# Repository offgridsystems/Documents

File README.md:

# DKblock documents -  
Here is the DK website for more information: https://dkblock922508958.wordpress.com 

Here is the ebay store for some parts. Let me know at the "Contact" tab of Wordpress (or ebay) if there is something else you would like.
https://www.ebay.com/sch/i.html?_from=R40&_trksid=p2380057.m570.l1313.TR0.TRC0.A0.H0.Xdkblock.TRS4&_nkw=dkblock&_sacat=0

All documents can be opened in OpenOffice format or Adobe Acrobat Reader. Some drawing files are in Alibre Design (for example AD_DRW extension). Please note that if your CAD program cannot read these files, not to worry because most CAD programs can output formats that can be read by other CAD programs, so please ask if you would like another format, we will try to accomodate.

All DKblock software and hardware is released as open source hardware (OSHW) as defined by the OSHWA: https://www.oshwa.org/definition/ and under the JSON license defined at https://www.json.org/license.html

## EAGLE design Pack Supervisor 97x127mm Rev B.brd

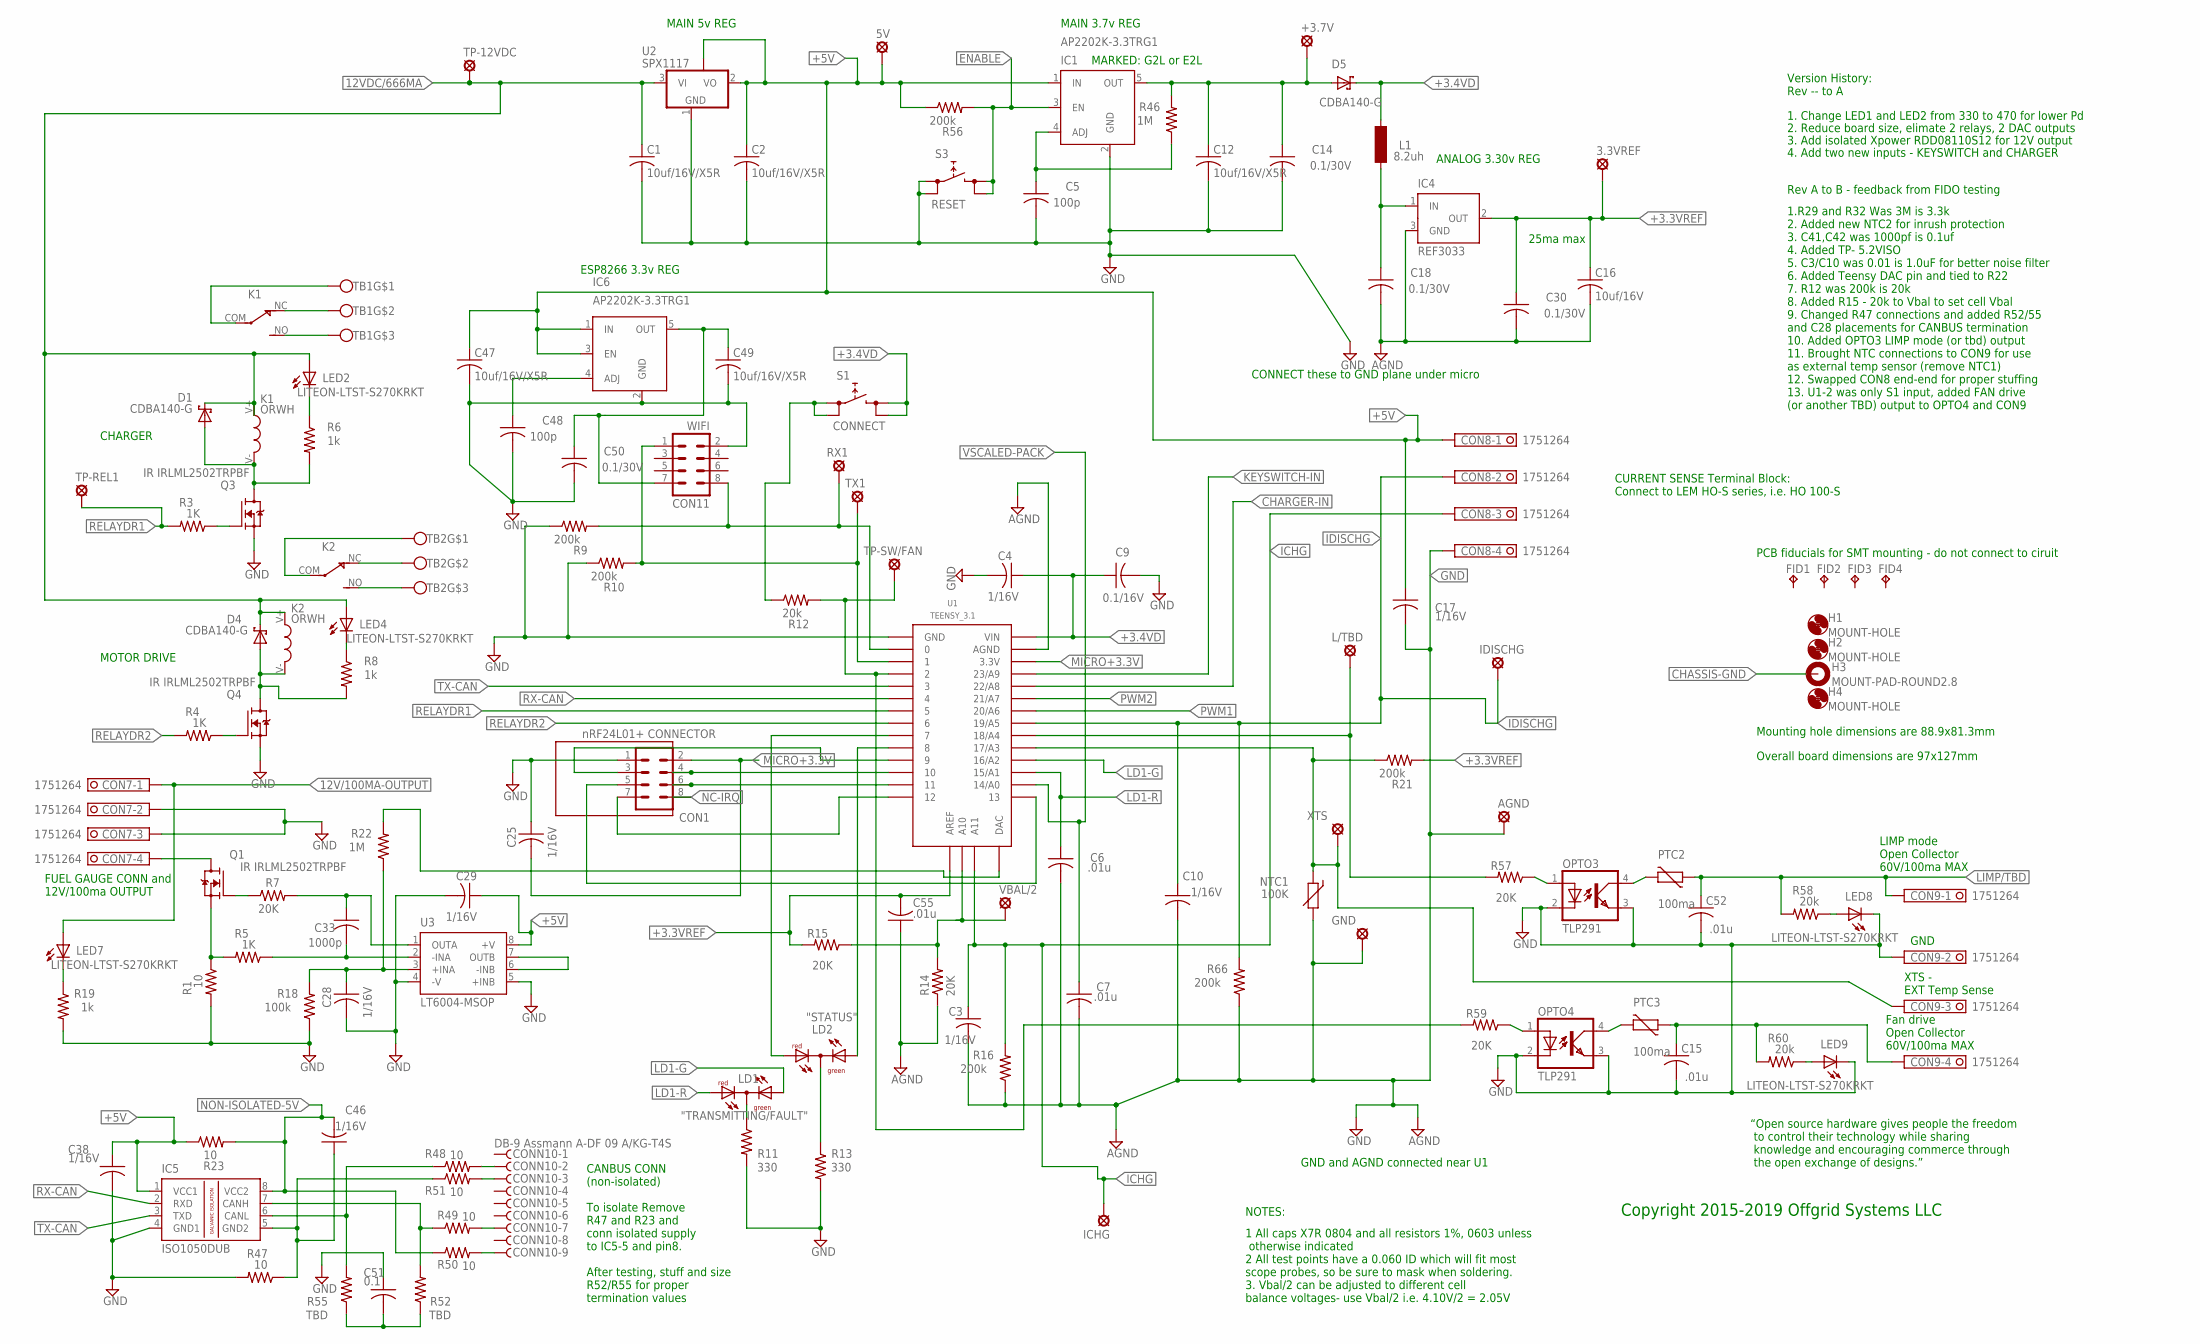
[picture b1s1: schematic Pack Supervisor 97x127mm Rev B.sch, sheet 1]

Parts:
3.3VREF, 5V: LSP10
+3.7V: LSP10
AGND: LSP10
C1, C2, C12, C47, C49: 10uf/16V/X5R; C0805K; MPN Murata GRM21BR61C106ME15L
C3, C10: 1/16V; TIMS_INDUCTOR_C0805; MPN Kemet C0805C103K5RACTU
C4, C17, C25, C28, C29, C38, C46: 1/16V; TIMS_INDUCTOR_C0805; MPN Kemet C0805C105K4RACTU
C5, C48: 100p; TIMS_INDUCTOR_C0805; MPN Kemet C0805C104K5RACTU
C6, C7, C15, C52: .01u; TIMS_INDUCTOR_C0805; MPN Kemet C0805C103K5RACTU
C9: 0.1/16V; TIMS_INDUCTOR_C0805; MPN Kemet C0805C104K5RACTU
C14, C18, C30, C50: 0.1/30V; TIMS_INDUCTOR_C0805; MPN Kemet C0805C104K5RACTU
C16: 10uf/16V; C0805K; MPN Murata GRM21BR61A476ME15L
C33: 1000p; TIMS_INDUCTOR_C0805; MPN Kemet C0805C105K4RACTU
C51: 0.1; TIMS_INDUCTOR_C0805; MPN Kemet C0805C105K4RACTU
C55: .01u; C0805; MPN Welwyn PCF0603R-3K01BT1
CON1: nRF24L01+ CONNECTOR; NRF24L01
CON7, CON8, CON9: 1751264
CON11: WIFI; MA04-2; MPN Sullins PPPC042LFBN-RC
CONN10: DB-9 Assmann A-DF 09 A/KG-T4S; H5M09RA; MPN ASSMANN A-DS 09 A/KG-T4S
D1, D4, D5: CDBA140-G; DO214AC; MPN comchip CDBA140-G
FID1, FID2, FID3, FID4: FIDUCIALTP10R; TP10R
GND: LSP10
H1: MOUNT-HOLE; 2,6; MPN Keystone 9056
H2, H4: MOUNT-HOLE; 2,6
H3: MOUNT-PAD-ROUND2.8; 2,8-PAD
IC1, IC6: AP2202K-3.3TRG1; SOT23-5; MPN Diodes AP2202K-3.3TRG1
IC4: REF3033; SOT23; MPN TI REF3033AIDBZR
IC5: ISO1050DUB; DUB-R-PDSO-G8; MPN TI ISO1050DUBR
ICHG: LSP10
IDISCHG: LSP10
K1, K2: ORWH; MPN TE 1461069-5
L1: 8.2uh; SM-1206; MPN Abracon AIML-1206-8R2K-T
L/TBD: LSP10
LD1: "TRANSMITTING/FAULT"; DUOLED-C-5MM; MPN Kingbright WP59EGC
LD2: "STATUS"; DUOLED-C-5MM; MPN Kingbright WP59EGC
LED2, LED4, LED7, LED8, LED9: LITEON-LTST-S270KRKT; MPN LiteOn LTST-S270KSKT
NTC1: 100K; 0603; MPN MURATA NCP18WF104J03RB
OPTO3, OPTO4: TLP291; MINI-FLAT-4
PTC2, PTC3: 100ma; CT/CN0603; MPN Bel Fuse 0ZCM0010FF2G
Q1, Q3, Q4: IRLML2502TRPBF; SOT23; MPN IR IRLML2502TRPBF
R1, R23, R47, R48, R49, R50, R51: 10; R0603; MPN Bourns CR0603-FX-10R0ELF
R3, R4, R5: 1K; R0603; MPN Bourns CR0603-FX-1001ELF
R6, R8, R19: 1k; R0603; MPN Bourns CR0603-FX-3300ELF
R7, R14, R15, R57, R59: 20K; R0603; MPN Bourns CR0603-FX-2002ELF
R9, R10, R16, R21, R56, R66: 200k; R0603; MPN Bourns CR0603-FX-2003ELF
R11, R13: 330; R0603; MPN Bourns CR0603-FX-3300ELF
R12: 20k; R0603; MPN Bourns CR0603-FX-2003ELF
R18: 100k; R0603; MPN Bourns CR0603-FX-1003ELF
R22, R46: 1M; R0603; MPN Bourns CR0603-FX-1004ELF
R52, R55: TBD; 0207/5V
R58, R60: 20k; R0603; MPN Bourns CR0603-FX-1001ELF
RX1: LSP10
S1: CONNECT; PTS645; MPN C&k PTS645SM43SMTR92 LFS
S3: RESET; PTS645; MPN C&k PTS645SM43SMTR92 LFS
TB1, TB2: TE-5-1437652-4; MPN TE 5-1437652-4
TP-12VDC: LSP10
TP-REL1: LSP10
TP-SW/FAN: LSP10
TX1: LSP10
U1: TEENSY_3.1; TEENSY_3.0-DIP+ANALOG+DAC; MPN OshPark Teensy 3.1
U2: SPX1117; SOT223; MPN Exar SPX1117M3-L-5-0/TR
U3: LT6004-MSOP; MPN LTC LT6004CMS8
VBAL/2: LSP10
XTS: LSP10

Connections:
0-UNUSED: CON11.8, R9.2, RX1.MP, U1.0
5V-ESP: C49.1, C50.1, CON11.7, IC6.5 (OUT)
12V/100MA-OUTPUT: CON7.1, LED7.ANODE (A); also elsewhere on the board
12VDC/666MA: C1.1, D1.C, D4.C, K1.V+, K2.V+, LED2.ANODE (A), LED4.ANODE (A), TP-12VDC.MP, U2.3 (VI); also elsewhere on the board
+3.3VREF: 3.3VREF.MP, C16.1, C30.1, C55.2, IC4.2 (OUT), R15.2, R21.2, U1.AREF; also elsewhere on the board
+3.4VD: C4.1, C9.1, D5.C, L1.2, S1.3, S1.4, U1.VIN; also elsewhere on the board
+3.65VD: +3.7V.MP, C12.1, C14.1, D5.A, IC1.5 (OUT), R46.2
+3.300VA: C18.1, IC4.1 (IN), L1.1
+5: CONN10.9, R50.2
+5V: 5V.MP, C2.1, C17.1, C29.1, C38.1, C47.1, CON8.1, IC1.1 (IN), IC5.1 (VCC1), IC6.1 (IN), IC6.3 (EN), R23.1, R56.1, U2.2 (VO), U2.4 (TAB), U3.8 (+V)
ADC-L3: L/TBD.MP, R57.2, U1.18/A4
ADS: D4.A, K2.V-, Q4.3 (D), R8.2
CE: CON1.3, U1.9
CHARGER-IN: U1.22/A8; also elsewhere on the board
CHASSIS-GND: H3.B2,8; also elsewhere on the board
CHI: CONN10.7, R49.2
CLO: CONN10.2, R48.2
CSN: CON1.4, U1.10
DAC: R22.2, U1.14 (DAC)
ENABLE: IC1.3 (EN), R56.2, S3.3, S3.4
FAN/TBD: C15.1, CON9.4, PTC3.1, R60.2
FUELGAUGE: CON7.4, Q1.3 (D)
G: CONN10.3, R51.2
GND: AGND.MP, C1.2, C2.2, C3.2, C4.2, C5.2, C6.2, C7.2, C9.2, C10.2, C12.2, C14.2, C15.2, C16.2, C17.2, C18.2, C25.1, C28.2, C29.2, C30.2, C38.2, C47.2, C48.2, C49.2, C50.2, C51.1, C52.2, C55.1, CON1.1, CON7.2, CON7.3, CON8.4, CON9.2, CON11.2, GND.MP, IC1.2 (GND), IC4.3 (GND), IC5.4 (GND1), IC6.2 (GND), LED8.CATHODE (C), LED9.CATHODE (C), NTC1.2, OPTO3.2 (C), OPTO3.3 (EMIT), OPTO4.2 (C), OPTO4.3 (EMIT), Q3.2 (S), Q4.2 (S), R1.2, R9.1, R10.1, R11.2, R13.2, R14.1, R16.1, R18.1, R19.2, R47.2, R66.1, S3.1, S3.2, U1.AGND, U1.GND, U2.1 (GND), U3.4 (-V), U3.5 (+INB); also elsewhere on the board
ICHG: C3.1, CON8.3, ICHG.MP, R16.2, U1.A11
IDISCHG: C10.1, CON8.2, IDISCHG.MP, R66.2, U1.19/A5
KEYSWITCH-IN: U1.23/A9; also elsewhere on the board
LD1-G: LD1.AX (AG), U1.16/A2
LD1-R: C6.1, LD1.AR, U1.15/A1
LIMP/TBD: C52.1, CON9.1, PTC2.1, R58.2
MICRO+3.3V: C25.2, CON1.2, U1.3.3V
MISO: CON1.7, U1.12
MOSI: CON1.6, U1.11
unnamed: LED2.CATHODE (C), R6.1
unnamed: CON9.3, NTC1.1, R21.1, U1.17/A3, XTS.MP
unnamed: IC5.6 (CANL), R48.1, R55.2
unnamed: K1.NC, TB1.2
unnamed: D1.A, K1.V-, Q3.3 (D), R6.2
unnamed: LD2.C, R13.1
unnamed: LD2.AX (AG), U1.8
unnamed: LD2.AR, U1.7
unnamed: U3.6 (-INB), U3.7 (OUTB)
unnamed: LD1.C, R11.1
unnamed: C28.1, R18.2, R22.1, U3.3 (+INA)
unnamed: Q3.1 (G), R3.1
unnamed: IC5.7 (CANH), R49.1, R52.2
unnamed: Q4.1 (G), R4.1
unnamed: C33.1, R7.2, U3.1 (OUTA)
unnamed: C5.1, IC1.4 (ADJ), R46.1
unnamed: Q1.1 (G), R7.1
unnamed: Q1.2 (S), R1.1, R5.2
unnamed: K1.NO, TB1.3
unnamed: K1.COM, TB1.1
unnamed: K2.COM, TB2.1
unnamed: K2.NC, TB2.2
unnamed: C33.2, R5.1, U3.2 (-INA)
unnamed: K2.NO, TB2.3
unnamed: LED4.CATHODE (C), R8.1
unnamed: C46.1, IC5.5 (GND2), R47.1, R51.1
unnamed: R12.2, R59.2, TP-SW/FAN.MP, U1.2
unnamed: C51.2, R52.1, R55.1
unnamed: CON11.1, R10.2, TX1.MP, U1.1
unnamed: LED7.CATHODE (C), R19.1
unnamed: C48.1, IC6.4 (ADJ)
unnamed: LED8.ANODE (A), R58.1
unnamed: OPTO3.1 (A), R57.1
unnamed: OPTO3.4 (COL), PTC2.2
unnamed: LED9.ANODE (A), R60.1
unnamed: OPTO4.1 (A), R59.1
unnamed: OPTO4.4 (COL), PTC3.2
unnamed: R12.1, S1.1, S1.2
NC-IRQ: CON1.8
NON-ISOLATED-5V: C46.2, IC5.8 (VCC2), R23.2, R50.1
PWM1: U1.20/A6; also elsewhere on the board
PWM2: U1.21/A7; also elsewhere on the board
RELAYDR1: R3.2, TP-REL1.MP, U1.5
RELAYDR2: R4.2, U1.6
RX-CAN: IC5.2 (RXD), U1.4
SCK: CON1.5, U1.13
TX-CAN: IC5.3 (TXD), U1.3
VBAL: R14.2, R15.1, U1.A10, VBAL/2.MP
VSCALED-PACK: C7.1, U1.14/A0; also elsewhere on the board

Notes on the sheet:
Copyright 2015-2019 Offgrid Systems LLC
GND and AGND connected near U1
NOTES:
1 All caps X7R 0804 and all resistors 1%, 0603 unless otherwise indicated 2 All test points have a 0.060 ID which will fit most scope probes, so be sure to mask when soldering. 3. Vbal/2 can be adjusted to different cell balance voltages- use Vbal/2 i.e. 4.10V/2 = 2.05V
Version History: Rev -- to A
CONNECT these to GND plane under micro
PCB fiducials for SMT mounting - do not connect to ciruit
1. Change LED1 and LED2 from 330 to 470 for lower Pd
2. Reduce board size, elimate 2 relays, 2 DAC outputs
3. Add isolated Xpower RDD08110S12 for 12V output
4. Add two new inputs - KEYSWITCH and CHARGER
25ma max
MAIN 5v REG
MAIN 3.7v REG
ANALOG 3.30v REG
ESP8266 3.3v REG
FUEL GAUGE CONN and 12V/100ma OUTPUT
CANBUS CONN (non-isolated) To isolate Remove R47 and R23 and conn isolated supply to IC5-5 and pin8. After testing, stuff and size R52/R55 for proper termination values
CURRENT SENSE Terminal Block: Connect to LEM HO-S series, i.e. HO 100-S
Rev A to B - feedback from FIDO testing
1.R29 and R32 Was 3M is 3.3k 2. Added new NTC2 for inrush protection 3. C41,C42 was 1000pf is 0.1uf 4. Added TP- 5.2VISO 5. C3/C10 was 0.01 is 1.0uF for better noise filter 6. Added Teensy DAC pin and tied to R22 7. R12 was 200k is 20k 8. Added R15 - 20k to Vbal to set cell Vbal 9. Changed R47 conn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
MOTOR DRIVE
CHARGER
Mounting hole dimensions are 88.9x81.3mm
“Open source hardware gives people the freedom to control their technology while sharing knowledge and encouraging commerce through the open exchange of designs.”
Overall board dimensions are 97x127mm
MARKED: G2L or E2L
LIMP mode Open Collector 60V/100ma MAX
XTS - EXT Temp Sense
GND
Fan drive Open Collector 60V/100ma MAX

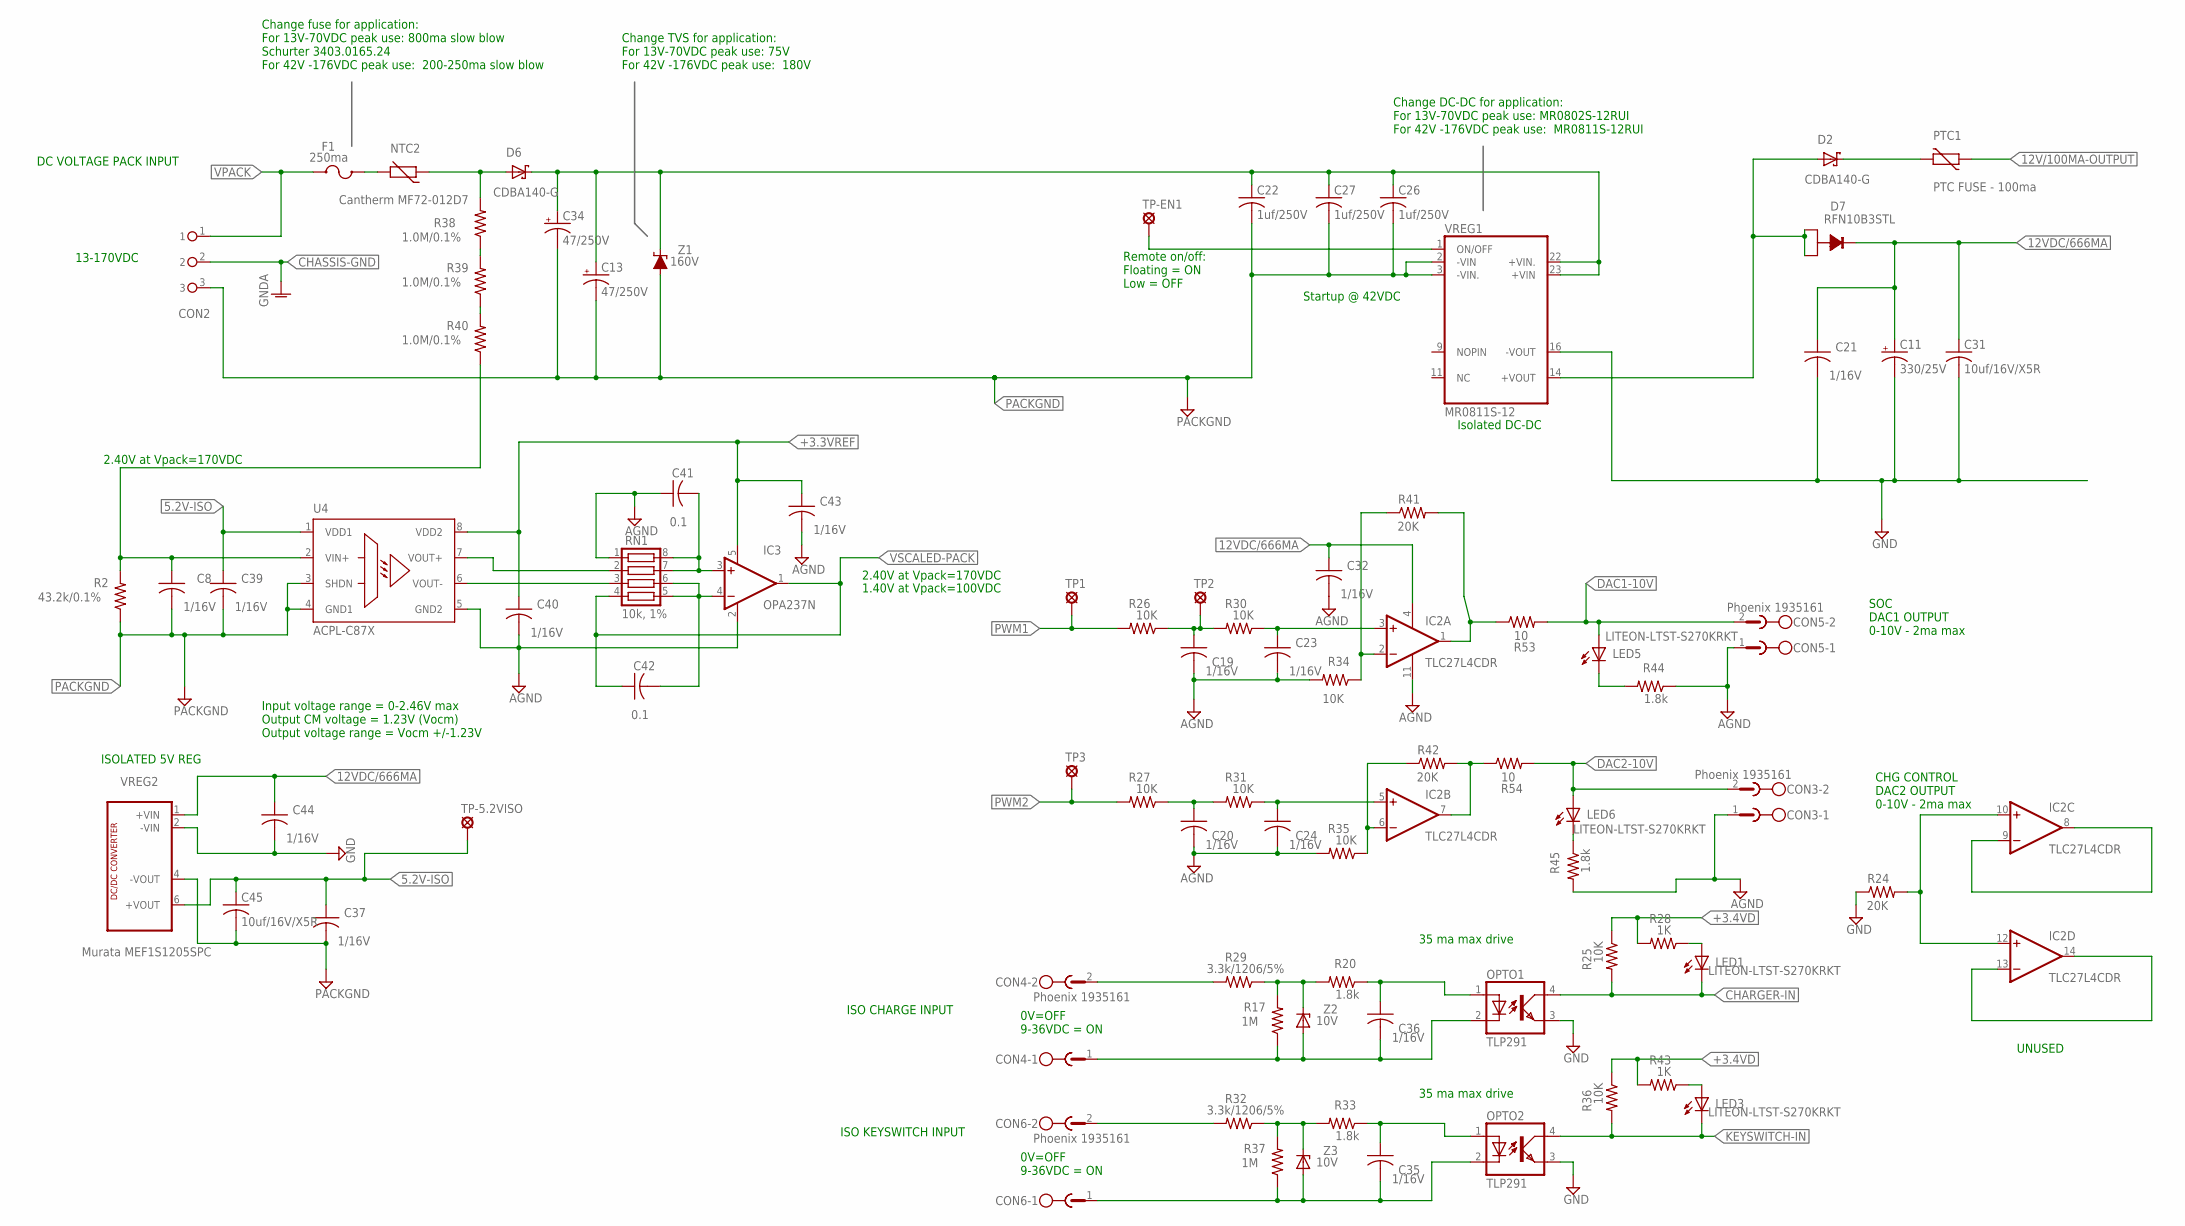
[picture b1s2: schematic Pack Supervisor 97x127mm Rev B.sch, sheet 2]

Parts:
C8, C19, C20, C21, C23, C24, C32, C35, C36, C37, C39, C40, C43, C44: 1/16V; TIMS_INDUCTOR_C0805; MPN Kemet C0805C105K4RACTU
C11: 330/25V; E5-10,5
C13, C34: 47/250V; E5-13; MPN PANASONIC ECA-2EM470
C22, C26, C27: 1uf/250V; RCL_C050-030X075
C31, C45: 10uf/16V/X5R; C0805K; MPN Murata GRM21BR61C106ME15L
C41, C42: 0.1; TIMS_INDUCTOR_C0805; MPN Kemet C0805C105K4RACTU
CON2: TYCO-796739-3
CON3, CON4, CON5, CON6: Phoenix 1935161; MSTBV2; MPN Phoenix 1935161
D2, D6: CDBA140-G; DO214AC; MPN comchip CDBA140-G
D7: RFN10B3STL; TO252-FATPADS; MPN ROHM RFN10B3STL
F1: 250ma; SCHURTER-UMT250; MPN Schurter 3403.0159.24
IC2: TLC27L4CDR; SO14; MPN TI TLC27L4CDR
IC3: OPA237N; SOT23-5; MPN TI OPA237NA/3K
LED1, LED3, LED5, LED6: LITEON-LTST-S270KRKT; MPN LiteOn LTST-S270KSKT
NTC2: Cantherm MF72-012D7; D7-PACKAGE
OPTO1, OPTO2: TLP291; MINI-FLAT-4
PTC1: PTC FUSE - 100ma; CT/CN0603; MPN Bel Fuse 0ZCM0010FF2G
R2: 43.2k/0.1%; R0603; MPN Panasonic ERA-3AEB4322V
R17, R37: 1M; R0603; MPN Bourns CR0603-FX-1004ELF
R20, R33, R44, R45: 1.8k; R0603; MPN Bourns CR0603-FX-1821ELF
R24, R41, R42: 20K; R0603; MPN Bourns CR0603-FX-2002ELF
R25, R26, R27, R30, R31, R34, R35, R36: 10K; R0603; MPN Bourns CR0603-FX-1002ELF
R28, R43: 1K; R0603; MPN Bourns CR0603-FX-1001ELF
R29, R32: 3.3k/1206/5%; R1206; MPN Panasonic ERJ-8GEYJ305V
R38, R39, R40: 1.0M/0.1%; R0805; MPN Panasonic ERA-6AEB105V
R53, R54: 10; R0603; MPN Bourns CR0603-FX-10R0ELF
RN1: 10k, 1%; CTS742C083; MPN Yageo TC164-FR-0710KL
TP1, TP2, TP3: LSP10
TP-5.2VISO: LSP10
TP-EN1: LSP10
U4: ACPL-C87X; STRETCH-SO8; MPN Avago Broadcomm ACPL-C87B-000E
VREG1: MR0811S-12; MPN Micropower Direct MR0811S-12RUI
VREG2: Murata MEF1S1205SPC; MURATA-MEF; MPN Murata MEF1S1205SPC
Z1: 160V; SMB; MPN ON SEMI 1SMB5954BT3G
Z2, Z3: 10V; TIMS_DIODE_SOT23; MPN ON SEMI SZBZX84C10LT1G

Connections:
5.2V-ISO: C37.1, C39.1, C45.1, TP-5.2VISO.MP, U4.1 (VDD1), VREG2.6 (+VOUT)
12V/100MA-OUTPUT: PTC1.1; also elsewhere on the board
12VDC/666MA: C11.+, C21.1, C31.1, C32.1, C44.1, D7.DRAIN (CATHODE), IC2.4 (V+), VREG2.1 (+VIN); also elsewhere on the board
+3.3VREF: C40.1, C43.1, IC3.5 (V+), U4.8 (VDD2); also elsewhere on the board
+3.4VD: R25.1, R28.2, R36.1, R43.2; also elsewhere on the board
ASDF: IC2.1 (OUT), R41.2, R53.1
CHARGER-IN: LED1.CATHODE (C), OPTO1.4 (COL), R25.2; also elsewhere on the board
CHASSIS-GND: CON2.2; also elsewhere on the board
CHGINLO: C36.2, CON4.1, OPTO1.2 (C), R17.1, Z2.1 (A)
DAC1-10V: CON5.2, LED5.ANODE (A), R53.2
DAC2-10V: CON3.2, LED6.ANODE (A), R54.2
GND: C11.-, C19.2, C20.2, C21.2, C23.2, C24.2, C31.2, C32.2, C40.2, C41.1, C43.2, C44.2, CON3.1, CON5.1, IC2.11 (V-), IC3.2 (V-), OPTO1.3 (EMIT), OPTO2.3 (EMIT), R24.1, R34.2, R35.2, R44.1, R45.2, RN1.1, U4.5 (GND2), VREG1.16 (-VOUT), VREG2.2 (-VIN); also elsewhere on the board
KEYSWINLO: C35.2, CON6.1, OPTO2.2 (C), R37.1, Z3.1 (A)
KEYSWITCH-IN: LED3.CATHODE (C), OPTO2.4 (COL), R36.2; also elsewhere on the board
unnamed: IC2.7 (OUT), R42.2, R54.1
unnamed: R38.1, R39.2
unnamed: R39.1, R40.2
unnamed: F1.P$1 (1A), NTC2.2
unnamed: IC2.2 (-IN), R34.1, R41.1
unnamed: C23.1, IC2.3 (+IN), R30.1
unnamed: CON4.2, R29.2
unnamed: TP-EN1.MP, VREG1.1 (ON/OFF)
unnamed: C36.1, OPTO1.1 (A), R20.1
unnamed: R17.2, R20.2, R29.1, Z2.3 (C)
unnamed: IC2.6 (-IN), R35.1, R42.1
unnamed: C24.1, IC2.5 (+IN), R31.1
unnamed: C20.1, R27.1, R31.2
unnamed: IC2.8 (OUT), IC2.9 (-IN)
unnamed: IC2.13 (-IN), IC2.14 (OUT)
unnamed: IC2.10 (+IN), IC2.12 (+IN), R24.2
unnamed: LED1.ANODE (A), R28.1
unnamed: C35.1, OPTO2.1 (A), R33.1
unnamed: R32.1, R33.2, R37.2, Z3.3 (C)
unnamed: LED3.ANODE (A), R43.1
unnamed: D2.C, PTC1.2
unnamed: C19.1, R26.1, R30.2, TP2.MP
unnamed: LED5.CATHODE (C), R44.2
unnamed: LED6.CATHODE (C), R45.1
unnamed: C8.1, R2.2, R40.1, U4.2 (VIN+)
unnamed: D2.A, D7.GATE (ANODE1), D7.SOURCE (ANODE2), VREG1.14 (+VOUT)
unnamed: RN1.2, U4.7 (VOUT+)
unnamed: RN1.3, U4.6 (VOUT-)
unnamed: C42.2, IC3.4 (-IN), RN1.5, RN1.6
unnamed: C41.2, IC3.3 (+IN), RN1.7, RN1.8
unnamed: CON6.2, R32.2
PACKGND: C8.2, C13.-, C22.2, C26.2, C27.2, C34.-, C37.2, C39.2, C45.2, CON2.3, R2.1, U4.3 (SHDN), U4.4 (GND1), VREG1.2 (-VIN), VREG1.3 (-VIN.), VREG2.4 (-VOUT), Z1.A
PWM1: R26.2, TP1.MP; also elsewhere on the board
PWM2: R27.2, TP3.MP; also elsewhere on the board
TPF1A: D6.A, NTC2.1, R38.2
VIN: C13.+, C22.1, C26.1, C27.1, C34.+, D6.C, VREG1.22 (+VIN.), VREG1.23 (+VIN), Z1.C
VPACK: CON2.1, F1.P$2 (2A)
VSCALED-PACK: C42.1, IC3.1 (OUT), RN1.4; also elsewhere on the board

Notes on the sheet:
Remote on/off: Floating = ON Low = OFF
13-170VDC
Change DC-DC for application: For 13V-70VDC peak use: MR0802S-12RUI For 42V -176VDC peak use: MR0811S-12RUI
Change fuse for application: For 13V-70VDC peak use: 800ma slow blow Schurter 3403.0165.24 For 42V -176VDC peak use: 200-250ma slow blow
Change TVS for application: For 13V-70VDC peak use: 75V For 42V -176VDC peak use: 180V
2.40V at Vpack=170VDC
0V=OFF 9-36VDC = ON
35 ma max drive
Input voltage range = 0-2.46V max Output CM voltage = 1.23V (Vocm) Output voltage range = Vocm +/-1.23V
Isolated DC-DC
Startup @ 42VDC
ISO KEYSWITCH INPUT
ISO CHARGE INPUT
SOC DAC1 OUTPUT 0-10V - 2ma max
CHG CONTROL DAC2 OUTPUT 0-10V - 2ma max
UNUSED
ISOLATED 5V REG
DC VOLTAGE PACK INPUT
1.40V at Vpack=100VDC

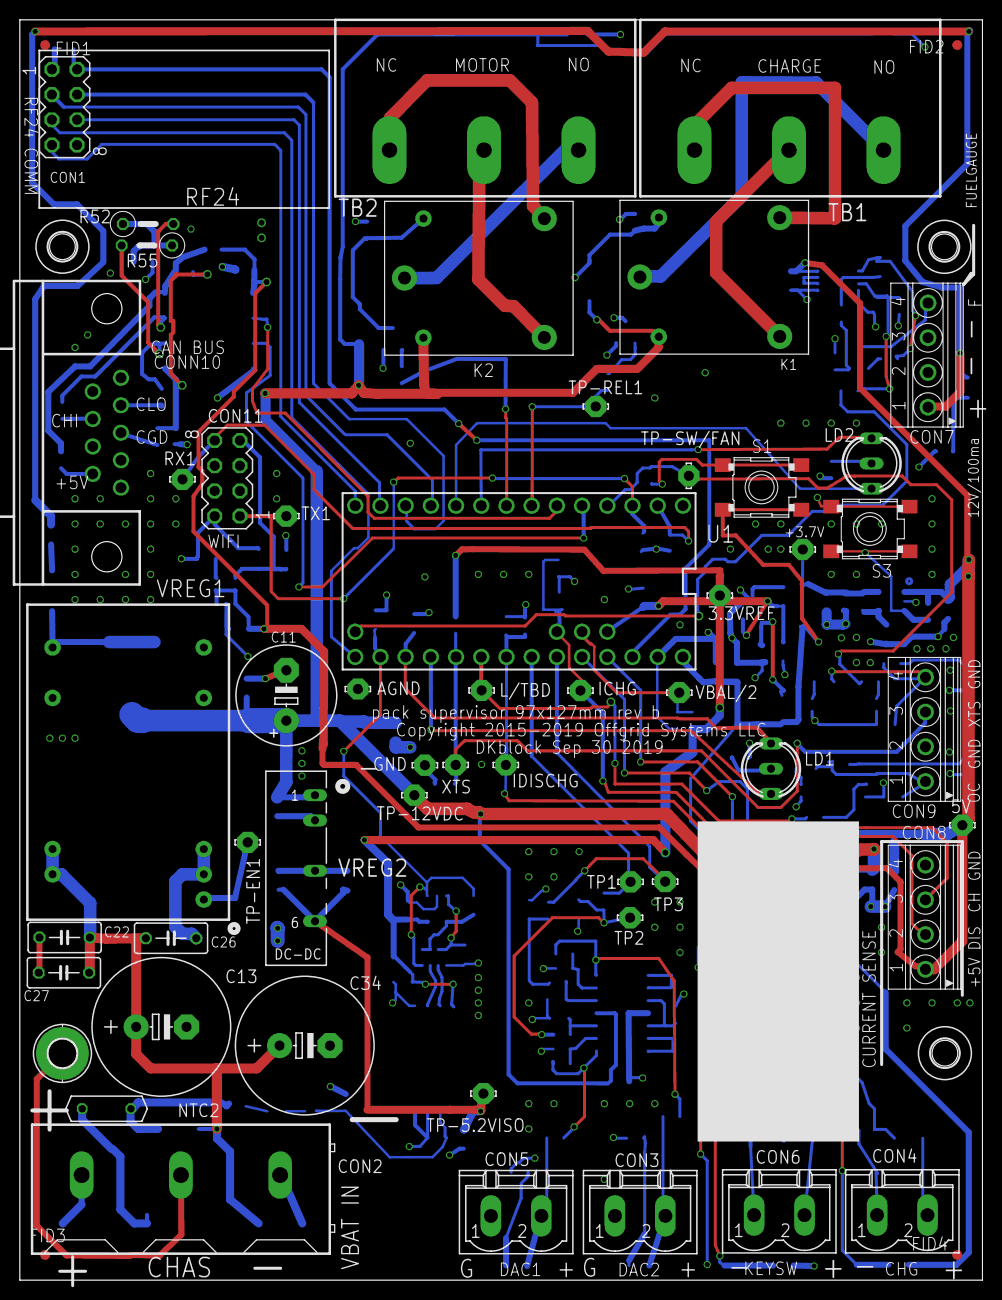
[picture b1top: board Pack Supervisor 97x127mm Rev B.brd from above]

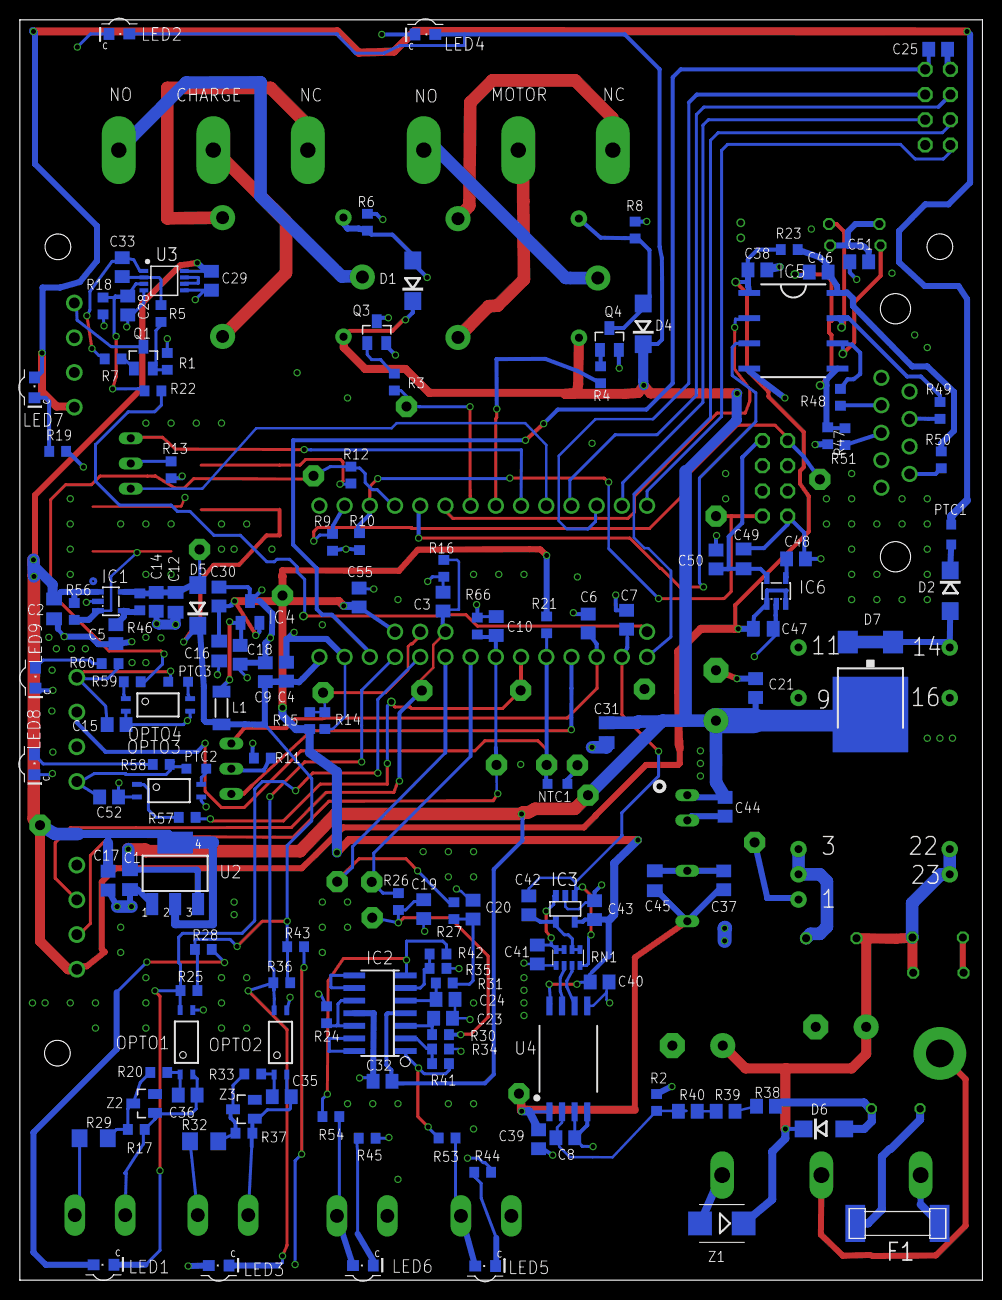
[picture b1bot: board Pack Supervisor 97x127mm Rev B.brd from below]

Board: 4 copper layers, 97.0 x 127.0 mm, 206 parts (147 on the bottom side), 122 nets.

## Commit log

2019-10-14 Initial Upload
2019-10-14 Add files via upload
    These are the design files to make the plastic mold for the DK cell holder - 20 cell design
2019-10-17 RevA Increased Thickness
    Bar was too thin. Increased to .13 inches.
2019-10-17 Incorrect
2019-10-17 Added tolerances
2019-10-17 outdated
2019-11-19 Lower cost version of 3 parallel block bus bar
2019-11-19 Lower cost 3 parallel block busbar
2019-11-19 Lowest cost 3 parallel block busbar
2019-11-19 Plastic mold
2019-11-19 Plastic injection mold
2019-11-20 Update for pic
2019-11-26 Add correct material drawings
2019-11-26 This file is an Alibre sheet metal part
2019-12-06 Updated for max and continuous current ratings
2019-12-06 Updated with maximum and continuous current ratings
2019-12-06 Update max and cont current ratings
2019-12-06 added max and continuous current rating
2019-12-10 Create Contributors code of conduct
2019-12-10 Update Contributors code of conduct
2019-12-21 Step file for DK spring
2019-12-21 BOM for all DKblock incl Pack Supervisor - min system
2019-12-22 Please read before using any of DKblock files
2019-12-22 updated for parts purchasing
2020-02-26 Getting started doc
2020-02-26 First file to read before build
2020-02-28 Saw shaker test- UUT almost vibrated out!
2020-05-18 Requested by user
